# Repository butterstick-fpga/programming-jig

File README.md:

# ButterStick Programming-jig

A simple FT232H based programming jig for the ButterStick.

---

## What is it

A simple jig made from PCBs that connects to a ButterStick with pogo-pins.

The board supports 
 - Programming/comms over JTAG.
 - Voltage sensing via an SPI ADC connected to the FT232H's I/O pins.

## Render

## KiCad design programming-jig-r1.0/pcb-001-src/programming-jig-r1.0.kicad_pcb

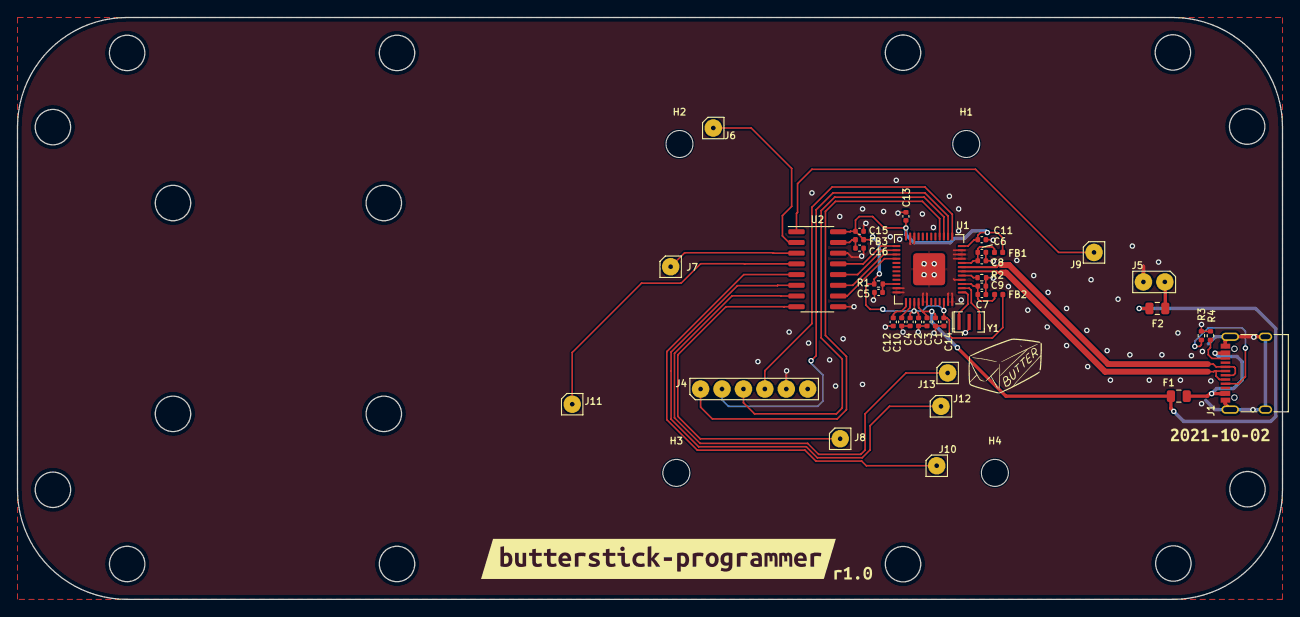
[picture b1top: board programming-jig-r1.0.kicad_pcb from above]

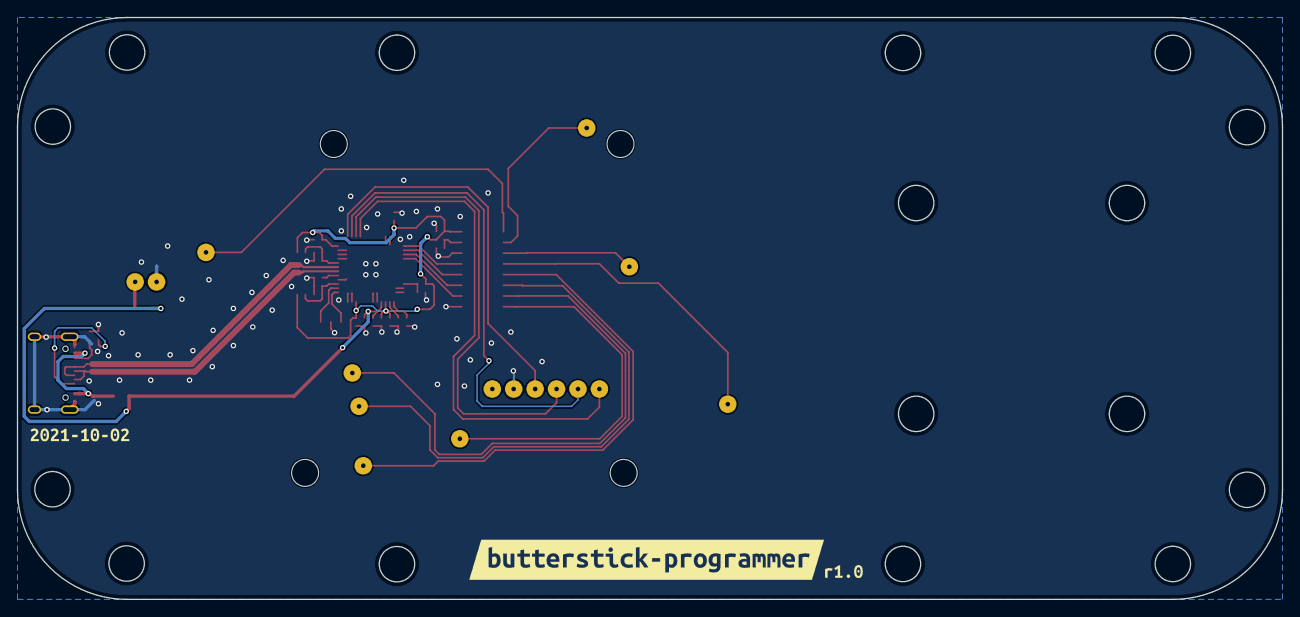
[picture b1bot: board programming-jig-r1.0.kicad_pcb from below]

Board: 2 copper layers, 150.0 x 69.0 mm, 49 parts (3 on the bottom side), 34 nets.

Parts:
C1, C2, C6, C7: 4.7uF; C_0402_1005Metric
C3, C4, C8, C9, C10, C11, C12, C13, C14, C15, C16: .1uF; C_0402_1005Metric
C5: 0.1uF; C_0402_1005Metric
F1, F2: Polyfuse_Small; Fuse_0805_2012Metric
FB1, FB2, FB3: Ferrite_Bead_Small; L_0402_1005Metric
H1, H2, H3, H4: MountingHole; MountingHole_3.2mm_M3_DIN965
J1: USB_C_Receptacle_USB2.0; USB_C_Receptacle_XKB_U262-16XN-4BVC11
J4: Conn_01x06_Male; 821-22-006-10-004101
J5: Conn_01x02_Male; 821-22-002-10-004101
J6, J7, J8, J9, J10, J11, J12, J13: Conn_01x01_Male; 0906-4-15-20-75-14-11-0
R1: 4.7K; R_0402_1005Metric
R2: 12K; R_0402_1005Metric
R3, R4: 5K1; R_0402_1005Metric
U1: FT232HQ; QFN-48-1EP_8x8mm_P0.5mm_EP6.2x6.2mm
U2: MCP3008; SOIC-16_3.9x9.9mm_P1.27mm
Y1: Resonator; Resonator_SMD_Murata_CSTxExxV-3Pin_3.0x1.1mm
kibuzzard-615A738C, kibuzzard-615A738C#2: G***; kibuzzard-615A738C
kibuzzard-615A7324, kibuzzard-615A7324#2: G***; kibuzzard-615A7324
kibuzzard-615A7371, kibuzzard-615A7371#2: G***; kibuzzard-615A7371

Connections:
+3.3VA: C2.1, C4.1, C11.1, C13.1, C14.1, C15.1, FB1.2, FB2.2, FB3.2, R1.2, U1.12 (VCCIO), U1.24 (VCCIO), U1.39 (VCCD), U1.46 (VCCIO), U2.16 (Vdd)
+5V: C1.1, C3.1, F1.1, F2.1, U1.40 (VREGIN)
/JTAG_TCK: J4.4, U1.13 (ADBUS0)
/JTAG_TDI: J4.2, U1.14 (ADBUS1)
/JTAG_TDO: J4.3, U1.15 (ADBUS2)
/JTAG_TMS: J4.1, U1.16 (ADBUS3)
/USB_D+: J1.A6 (D+), J1.B6 (D+), U1.7 (DP)
/USB_D-: J1.A7 (D-), J1.B7 (D-), U1.6 (DM)
/VCCA: C12.1, U1.37 (VCCA)
/VCORE: C10.1, U1.38 (VCCCORE)
GND: C1.2, C2.2, C3.2, C4.2, C5.2, C6.2, C7.2, C8.2, C9.2, C10.2, C11.2, C12.2, C13.2, C14.2, C15.2, C16.2, J1.A1 (GND), J1.A12 (GND), J1.B1 (GND), J1.B12 (GND), J1.S1 (SHIELD), J4.5, J5.2, R2.1, R3.2, R4.2, U1.4 (AGND), U1.9 (AGND), U1.10 (GND), U1.11 (GND), U1.22 (GND), U1.23 (GND), U1.35 (GND), U1.36 (GND), U1.41 (AGND), U1.42 (TEST), U1.47 (GND), U1.48 (GND), U1.49 (GND), U2.9 (DGND), U2.14 (AGND), Y1.2
unnamed: C5.1, R1.1, U1.34 (~RESET)
unnamed: C6.1, C8.1, FB1.1, U1.8 (VPLL)
unnamed: C7.1, C9.1, FB2.1, U1.3 (VPHY)
unnamed: C16.1, FB3.1, U2.15 (Vref)
unnamed: F1.2, J1.A4 (VBUS), J1.A9 (VBUS), J1.B4 (VBUS), J1.B9 (VBUS)
unnamed: J1.A5 (CC1), R3.1
unnamed: J1.B5 (CC2), R4.1
unnamed: F2.2, J5.1
unnamed: R2.2, U1.5 (REF)
unnamed: U1.1 (XCSI), Y1.1
unnamed: U1.2 (XCSO), Y1.3
unnamed: U1.25 (ACBUS1), U2.13 (CLK)
unnamed: U1.26 (ACBUS2), U2.12 (Dout)
unnamed: U1.27 (ACBUS3), U2.11 (Din)
unnamed: U1.28 (ACBUS4), U2.10 (~CS/SHDN)
unnamed: J9.1, U2.1 (CH0)
unnamed: J6.1, U2.2 (CH1)
unnamed: J7.1, U2.3 (CH2)
unnamed: J11.1, U2.4 (CH3)
unnamed: J10.1, U2.5 (CH4)
unnamed: J12.1, U2.6 (CH5)
unnamed: J13.1, U2.7 (CH6)
unnamed: J8.1, U2.8 (CH7)
